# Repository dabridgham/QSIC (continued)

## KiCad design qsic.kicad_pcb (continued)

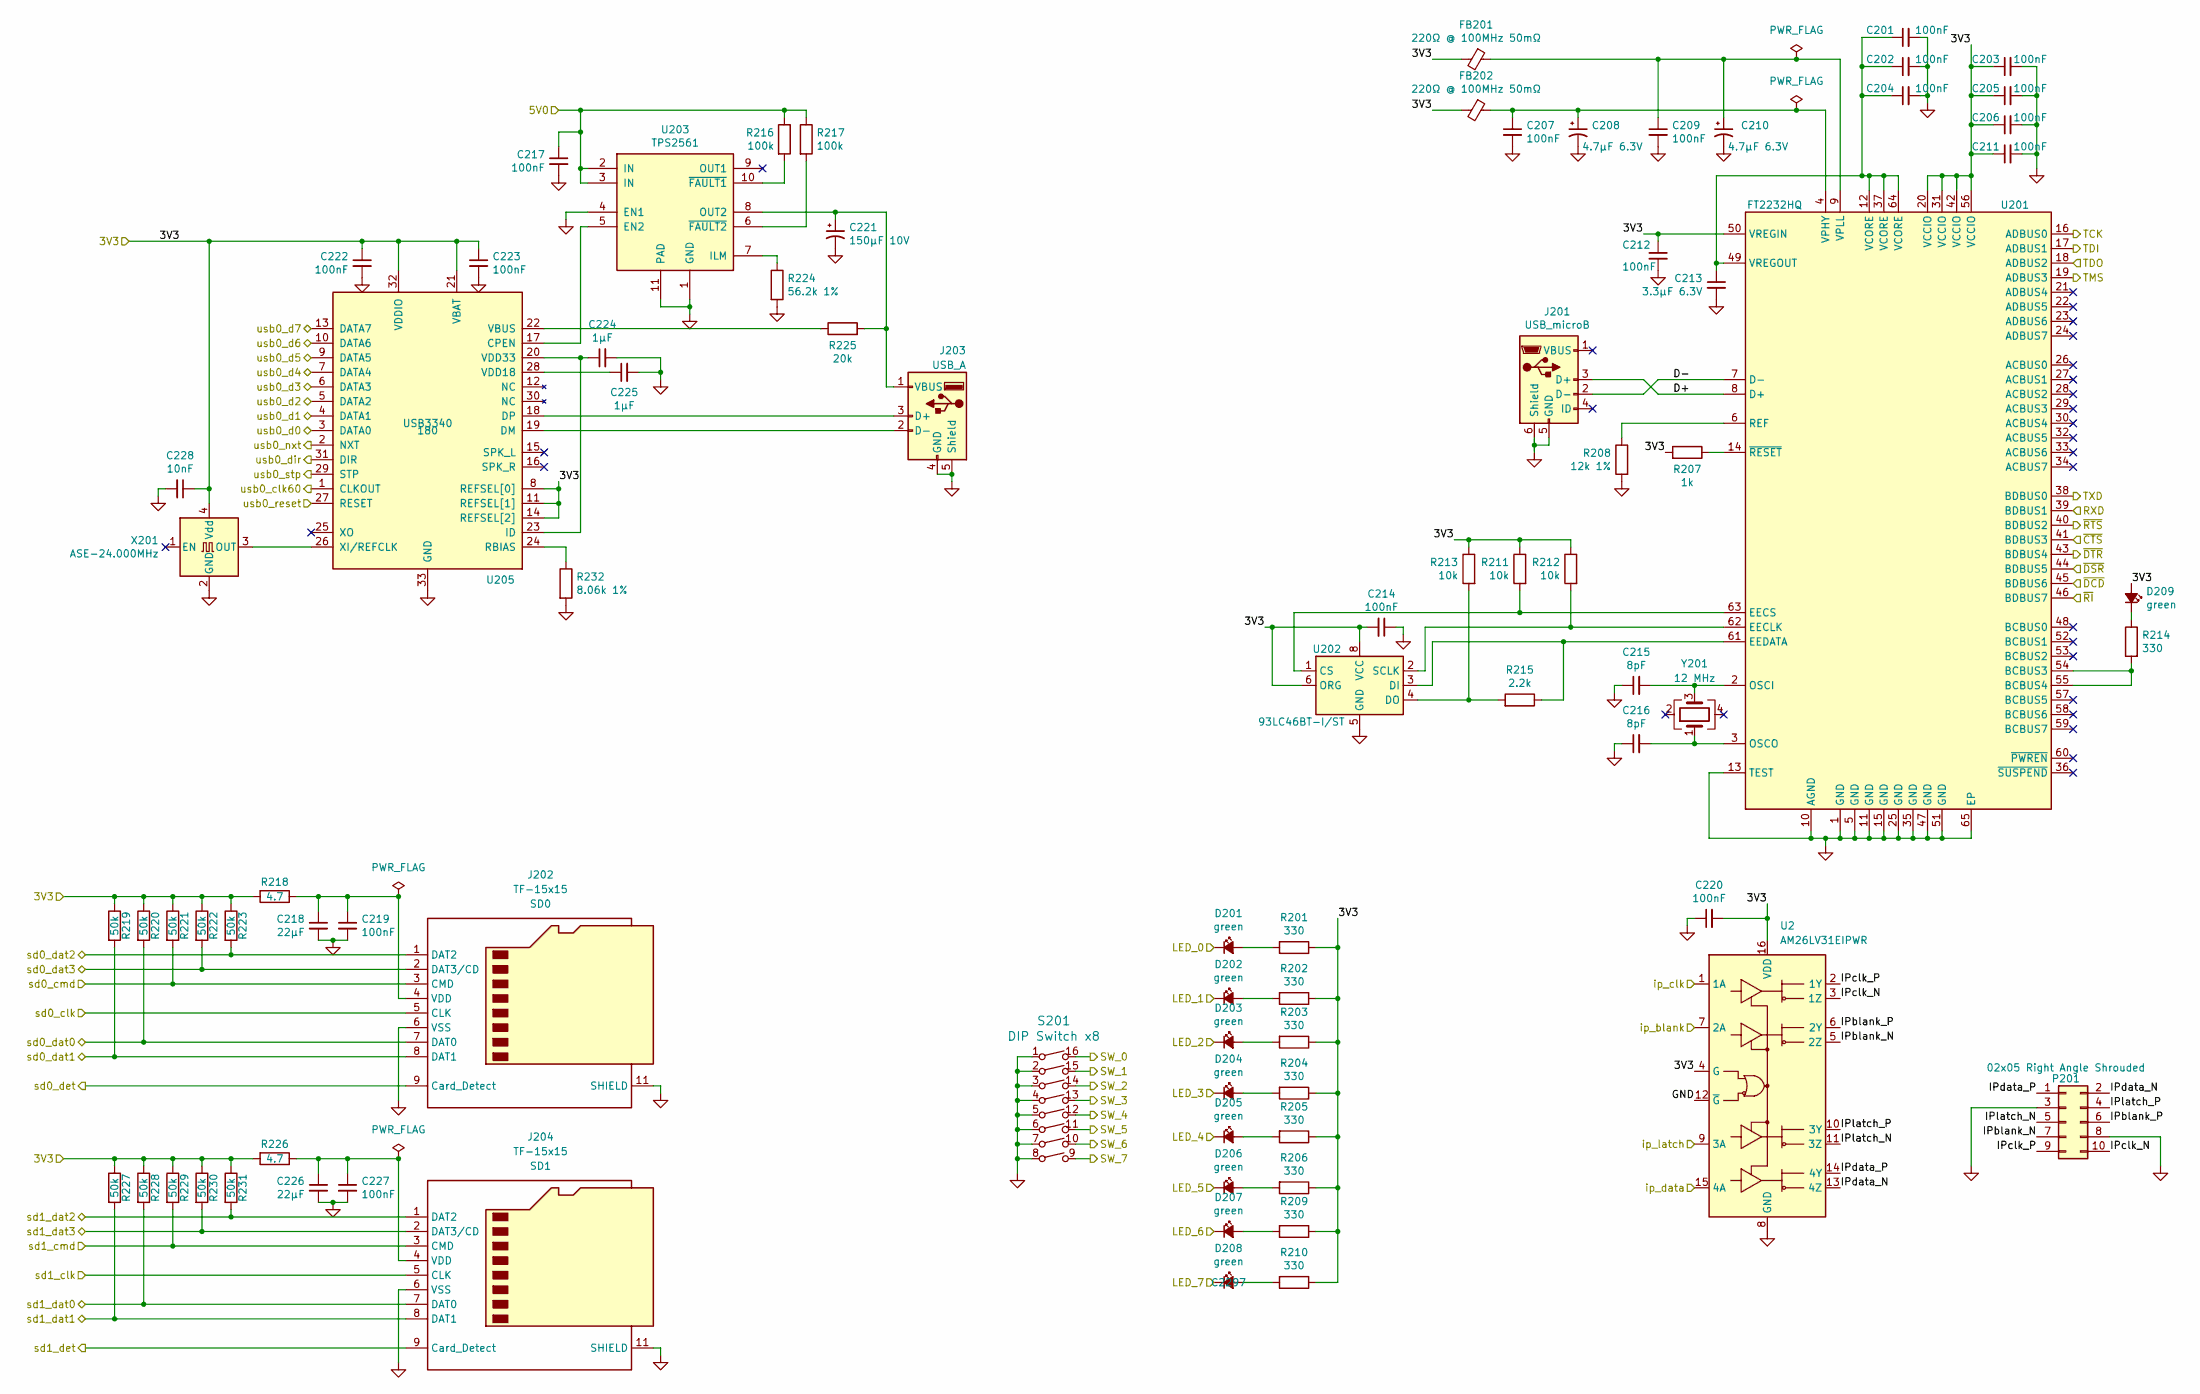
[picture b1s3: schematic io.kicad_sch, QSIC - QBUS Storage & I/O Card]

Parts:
C201, C202, C203, C204, C205, C206, C207, C209, C211, C212, C214, C217, C219, C220, C222, C223, C227: 100nF; C_0603_1608Metric; MPN CL10B104KO8NNNC
C208, C210: 4.7µF 6.3V; C_0603_1608Metric; MPN CL10A475KP8NNNC; JLCPCB Part C19666
C213: 3.3µF 6.3V; C_0603_1608Metric; MPN CL10A335KP8NNNC; JLCPCB Part C51412
C215, C216: 8pF; C_0603_1608Metric; MPN CL10C8R2DB8NNNC
C218, C226: 22µF; C_0603_1608Metric; MPN CL10A226MP8NUNE; JLCPCB Part C59461
C221: 150µF 10V; C_Elec_6.3x7.7; MPN EEEFTV151XAP; JLCPCB Part C178603
C224, C225: 1µF; C_0603_1608Metric; MPN CL10B105KO8NNNC; JLCPCB Part C15849
C228: 10nF; C_0603_1608Metric; MPN CL10B103KB8NNNC
D201, D202, D203, D204, D205, D206, D207, D208, D209: green; LED_0603_1608Metric; MPN LTST-C190KGKT; JLCPCB Part C2297
FB201, FB202: 220Ω @ 100MHz 50mΩ; L_0805_2012Metric; MPN 742792022; JLCPCB Part C2661452
J201: USB_microB; USB_Micro-B_Molex_47346-0001; MPN 47346-0001; JLCPCB Part C132560
J202, J204: TF-15x15; TF15X15
J203: USB_A; Amphenol_87583_USB_A; MPN 87583-3010; JLCPCB Part C599120
P201: 02x05 Right Angle Shrouded; Box_Header_2x05_P2.54mm; MPN SBH11-PBPC-D05-RA-BK; JLCPCB Part C7434504
R201, R202, R203, R204, R205, R206, R209, R210, R214: 330; R_0603_1608Metric; MPN RC0603FR-07330RL
R207: 1k; R_0603_1608Metric; MPN RC0603FR-071KL
R208: 12k 1%; R_0603_1608Metric; MPN RC0603FR-0712KL
R211, R212, R213: 10k; R_0603_1608Metric; MPN RC0603FR-0710KL
R215: 2.2k; R_0603_1608Metric; MPN RC0603FR-072K2L
R216, R217: 100k; R_0603_1608Metric; MPN RC0603FR-07100KL
R218, R226: 4.7; R_0603_1608Metric; MPN RC0603FR-074R7L
R219, R220, R221, R222, R223, R227, R228, R229, R230, R231: 50k; R_0603_1608Metric; MPN RC0603FR-0749K9L
R224: 56.2k 1%; R_0603_1608Metric; MPN RC0603FR-0756K2L; JLCPCB Part C482887
R225: 20k; R_0603_1608Metric; MPN RC0603FR-0720KL
R232: 8.06k 1%; R_0603_1608Metric; MPN RC0603FR-078K06L; JLCPCB Part C131052
S201: DIP Switch x8; SW_DIP_SPSTx08_Slide_Omron_A6S-810x_W8.9mm_P2.54mm; MPN A6S-8101-H; JLCPCB Part C319032
U2: AM26LV31EIPWR; TSSOP-16_4.4x5mm_P0.65mm; MPN AM26LV31EIPWR; JLCPCB Part C527447
U201: FT2232HQ; QFN-64-1EP_9x9mm_P0.5mm_EP4.35x4.35mm_ThermalVias; MPN FT2232HQ
U202: 93LC46BT-I/ST; TSSOP-8_4.4x3mm_P0.65mm; MPN 93LC46BC-IST
U203: TPS2561; VSON-10-1EP_3x3mm_P0.5mm_EP1.65x2.4mm_ThermalVias; MPN TPS2561DRCR
U205: USB3340; QFN-32-1EP_5x5mm_P0.5mm_EP3.3x3.3mm; MPN USB3340-EZK
X201: ASE-24.000MHz; Oscillator_SMD_Abracon_ASE-4Pin_3.2x2.5mm; MPN ASE-24.000MHZ-LC-T
Y201: 12 MHz; Crystal_SMD_Abracon_ABM10-4Pin_2.5x2.0mm; MPN ABM10-167-12.000MHZ-T3

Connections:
/3V3: C203.1, C205.1, C206.1, C211.1, C212.1, C214.2, C220.2, C222.1, C223.1, C228.1, D209.2 (A), FB201.2, FB202.2, R201.1, R202.1, R203.1, R204.1, R205.1, R206.1, R207.2, R209.1, R210.1, R211.1, R212.1, R213.1, R218.2, R219.1, R220.1, R221.1, R222.1, R223.1, R226.2, R227.1, R228.1, R229.1, R230.1, R231.1, U2.4 (G), U2.16 (VDD), U201.20 (VCCIO), U201.31 (VCCIO), U201.42 (VCCIO), U201.50 (VREGIN), U201.56 (VCCIO), U202.6 (ORG), U202.8 (VCC), U205.8 (REFSEL[0]), U205.11 (REFSEL[1]), U205.14 (REFSEL[2]), U205.21 (VBAT), U205.32 (VDDIO), X201.4 (Vdd); also elsewhere on the board
/5V0: C217.1, R216.1, R217.1, U203.2 (IN), U203.3 (IN); also elsewhere on the board
/IO/D+: J201.3 (D+), U201.8 (D+)
/IO/D-: J201.2 (D-), U201.7 (D-)
/IO/IPblank_N: P201.7, U2.5 (2Z)
/IO/IPblank_P: P201.6, U2.6 (2Y)
/IO/IPclk_N: P201.10, U2.3 (1Z)
/IO/IPclk_P: P201.9, U2.2 (1Y)
/IO/IPdata_N: P201.2, U2.13 (4Z)
/IO/IPdata_P: P201.1, U2.14 (4Y)
/IO/IPlatch_N: P201.5, U2.11 (3Z)
/IO/IPlatch_P: P201.4, U2.10 (3Y)
/LED_0: D201.1 (K); also elsewhere on the board
/LED_1: D202.1 (K); also elsewhere on the board
/LED_2: D203.1 (K); also elsewhere on the board
/LED_3: D204.1 (K); also elsewhere on the board
/LED_4: D205.1 (K); also elsewhere on the board
/LED_5: D206.1 (K); also elsewhere on the board
/LED_6: D207.1 (K); also elsewhere on the board
/LED_7: D208.1 (K); also elsewhere on the board
/RXD: U201.39 (BDBUS1); also elsewhere on the board
/SW_0: S201.16; also elsewhere on the board
/SW_1: S201.15; also elsewhere on the board
/SW_2: S201.14; also elsewhere on the board
/SW_3: S201.13; also elsewhere on the board
/SW_4: S201.12; also elsewhere on the board
/SW_5: S201.11; also elsewhere on the board
/SW_6: S201.10; also elsewhere on the board
/SW_7: S201.9; also elsewhere on the board
/TCK: U201.16 (ADBUS0); also elsewhere on the board
/TDI: U201.17 (ADBUS1); also elsewhere on the board
/TDO: U201.18 (ADBUS2); also elsewhere on the board
/TMS: U201.19 (ADBUS3); also elsewhere on the board
/TXD: U201.38 (BDBUS0); also elsewhere on the board
/ip_blank: U2.7 (2A); also elsewhere on the board
/ip_clk: U2.1 (1A); also elsewhere on the board
/ip_data: U2.15 (4A); also elsewhere on the board
/ip_latch: U2.9 (3A); also elsewhere on the board
/sd0_clk: J202.5 (CLK); also elsewhere on the board
/sd0_cmd: J202.3 (CMD), R221.2; also elsewhere on the board
/sd0_dat0: J202.7 (DAT0), R220.2; also elsewhere on the board
/sd0_dat1: J202.8 (DAT1), R219.2; also elsewhere on the board
/sd0_dat2: J202.1 (DAT2), R223.2; also elsewhere on the board
/sd0_dat3: J202.2 (DAT3/CD), R222.2; also elsewhere on the board
/sd0_det: J202.9 (Card_Detect); also elsewhere on the board
/sd1_clk: J204.5 (CLK); also elsewhere on the board
/sd1_cmd: J204.3 (CMD), R229.2; also elsewhere on the board
/sd1_dat0: J204.7 (DAT0), R228.2; also elsewhere on the board
/sd1_dat1: J204.8 (DAT1), R227.2; also elsewhere on the board
/sd1_dat2: J204.1 (DAT2), R231.2; also elsewhere on the board
/sd1_dat3: J204.2 (DAT3/CD), R230.2; also elsewhere on the board
/sd1_det: J204.9 (Card_Detect); also elsewhere on the board
/usb0_clk60: U205.1 (CLKOUT); also elsewhere on the board
/usb0_d0: U205.3 (DATA0); also elsewhere on the board
/usb0_d1: U205.4 (DATA1); also elsewhere on the board
/usb0_d2: U205.5 (DATA2); also elsewhere on the board
/usb0_d3: U205.6 (DATA3); also elsewhere on the board
/usb0_d4: U205.7 (DATA4); also elsewhere on the board
/usb0_d5: U205.9 (DATA5); also elsewhere on the board
/usb0_d6: U205.10 (DATA6); also elsewhere on the board
/usb0_d7: U205.13 (DATA7); also elsewhere on the board
/usb0_dir: U205.31 (DIR); also elsewhere on the board
/usb0_nxt: U205.2 (NXT); also elsewhere on the board
/usb0_reset: U205.27 (RESET); also elsewhere on the board
/usp0_stp: U205.29 (STP); also elsewhere on the board
/~CTS: U201.41 (BDBUS3); also elsewhere on the board
/~DCD: U201.45 (BDBUS6); also elsewhere on the board
/~DSR: U201.44 (BDBUS5); also elsewhere on the board
/~DTR: U201.43 (BDBUS4); also elsewhere on the board
/~RI: U201.46 (BDBUS7); also elsewhere on the board
/~RTS: U201.40 (BDBUS2); also elsewhere on the board
GND: C201.2, C202.2, C203.2, C204.2, C205.2, C206.2, C207.2, C208.2, C209.2, C210.2, C211.2, C212.2, C213.2, C214.1, C215.1, C216.1, C217.2, C218.2, C219.2, C220.1, C221.2, C222.2, C223.2, C224.2, C225.2, C226.2, C227.2, C228.2, J201.5 (GND), J201.6 (Shield), J202.6 (VSS), J202.11 (SHIELD), J203.4 (GND), J203.5 (Shield), J204.6 (VSS), J204.11 (SHIELD), P201.3, P201.8, R208.2, R224.2, R232.2, S201.1, S201.2, S201.3, S201.4, S201.5, S201.6, S201.7, S201.8, U2.8 (GND), U2.12 (~G), U201.1 (GND), U201.5 (GND), U201.10 (AGND), U201.11 (GND), U201.13 (TEST), U201.15 (GND), U201.25 (GND), U201.35 (GND), U201.47 (GND), U201.51 (GND), U201.65 (EP), U202.5 (GND), U203.1 (GND), U203.4 (EN1), U203.11 (PAD), U205.33 (GND), X201.2 (GND); also elsewhere on the board
unnamed: D201.2 (A), R201.2
unnamed: D202.2 (A), R202.2
unnamed: D203.2 (A), R203.2
unnamed: D204.2 (A), R204.2
unnamed: D205.2 (A), R205.2
unnamed: D206.2 (A), R206.2
unnamed: D207.2 (A), R209.2
unnamed: D208.2 (A), R210.2
unnamed: D209.1 (K), R214.1
unnamed: C218.1, C219.1, J202.4 (VDD), R218.1
unnamed: J203.3 (D+), U205.18 (DP)
unnamed: J203.2 (D-), U205.19 (DM)
unnamed: C221.1, J203.1 (VBUS), R225.2, U203.8 (OUT2)
unnamed: C226.1, C227.1, J204.4 (VDD), R226.1
unnamed: R214.2, U201.54 (BCBUS3), U201.55 (BCBUS4)
unnamed: R212.2, U201.62 (EECLK), U202.2 (SCLK)
unnamed: R211.2, U201.63 (EECS), U202.1 (CS)
unnamed: R215.1, U201.61 (EEDATA), U202.3 (DI)
unnamed: C215.2, U201.2 (OSCI), Y201.3
unnamed: C216.2, U201.3 (OSCO), Y201.1
unnamed: R208.1, U201.6 (REF)
unnamed: C207.1, C208.1, FB202.1, U201.4 (VPHY)
unnamed: C209.1, C210.1, FB201.1, U201.9 (VPLL)
unnamed: C201.1, C202.1, C204.1, C213.1, U201.12 (VCORE), U201.37 (VCORE), U201.49 (VREGOUT), U201.64 (VCORE)
unnamed: R207.1, U201.14 (~RESET)
unnamed: R213.2, R215.2, U202.4 (DO)
unnamed: U203.5 (EN2), U205.17 (CPEN)
unnamed: R224.1, U203.7 (ILM)
unnamed: R216.2, U203.10 (~FAULT1)
unnamed: R217.2, U203.6 (~FAULT2)
unnamed: C224.1, U205.20 (VDD33), U205.23 (ID)
unnamed: R232.1, U205.24 (RBIAS)
unnamed: R225.1, U205.22 (VBUS)
unnamed: C225.1, U205.28 (VDD18)
unnamed: U205.26 (XI/REFCLK), X201.3 (OUT)

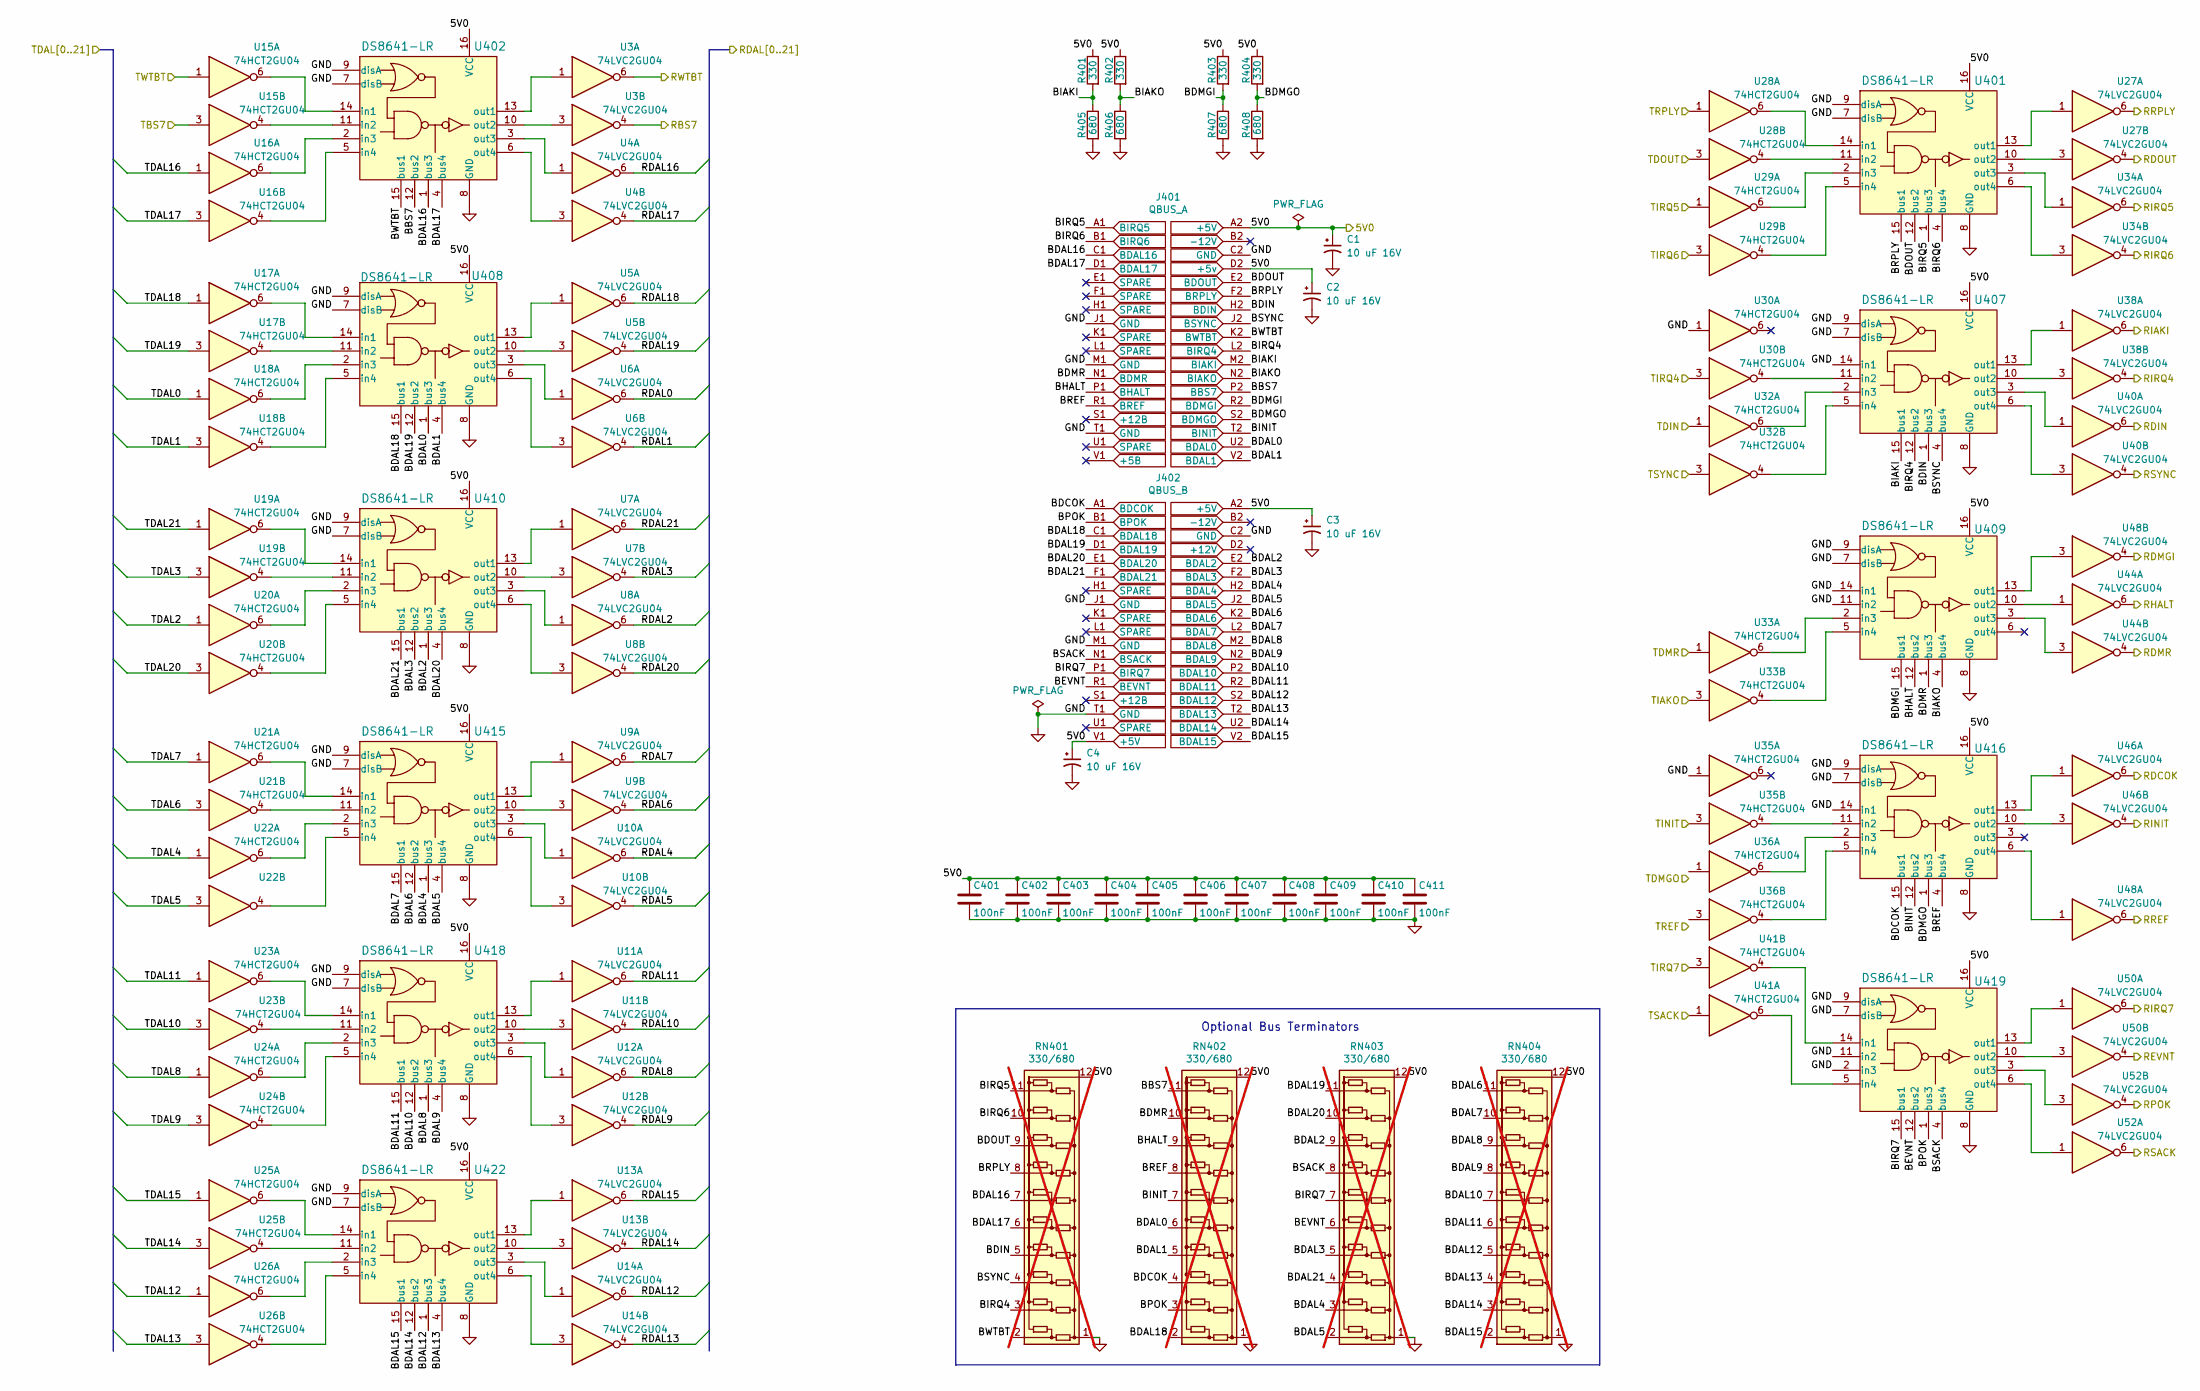
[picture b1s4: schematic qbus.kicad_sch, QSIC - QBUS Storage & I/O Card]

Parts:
C1, C2, C3, C4: 10 uF 16V; CP_EIA-3216-18_Kemet-A
C401, C402, C403, C404, C405, C406, C407, C408, C409, C410, C411: 100nF; C_0603_1608Metric; MPN CL10B104KO8NNNC
J401: QBUS_A; DEC_Edge_Fingers_single_height-1
J402: QBUS_B; DEC_Edge_Fingers_single_height-1
R401, R402, R403, R404: 330; R_0603_1608Metric; MPN RC0603FR-07330RL
R405, R406, R407, R408: 680; R_0603_1608Metric; MPN RC0603FR-07680RL
RN401, RN402, RN403, RN404: 330/680; R_Array_SIP12; MPN 4612X-104-331/681L; not fitted
U3, U4, U5, U6, U7, U8, U9, U10, U11, U12, U13, U14, U27, U34, U38, U40, U44, U46, U48, U50, U52: 74LVC2GU04; SOT-363_SC-70-6
U15, U16, U17, U18, U19, U20, U21, U22, U23, U24, U25, U26, U28, U29, U30, U32, U33, U35, U36, U41: 74HCT2GU04; SOT-363_SC-70-6
U401, U402, U407, U408, U409, U410, U415, U416, U418, U419, U422: DS8641-LR; DIP-16_W7.62mm; MPN DS8641

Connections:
/5V0: C1.1, C2.1, C3.1, C4.1, C401.1, C402.1, C403.1, C404.1, C405.1, C406.1, C407.1, C408.1, C409.1, C410.1, C411.1, J401.A2 (+5V), J401.D2 (+5v), J402.A2 (+5V), J402.V1 (+5V), R401.1, R402.1, R403.1, R404.1, RN401.12 (COM2), RN402.12 (COM2), RN403.12 (COM2), RN404.12 (COM2), U401.16 (VCC), U402.16 (VCC), U407.16 (VCC), U408.16 (VCC), U409.16 (VCC), U410.16 (VCC), U415.16 (VCC), U416.16 (VCC), U418.16 (VCC), U419.16 (VCC), U422.16 (VCC); also elsewhere on the board
/QBUS/BBS7: J401.P2 (BBS7), RN402.11 (R10), U402.12 (bus2)
/QBUS/BDAL0: J401.U2 (BDAL0), RN402.6 (R5), U408.1 (bus3)
/QBUS/BDAL1: J401.V2 (BDAL1), RN402.5 (R4), U408.4 (bus4)
/QBUS/BDAL2: J402.E2 (BDAL2), RN403.9 (R8), U410.1 (bus3)
/QBUS/BDAL3: J402.F2 (BDAL3), RN403.5 (R4), U410.12 (bus2)
/QBUS/BDAL4: J402.H2 (BDAL4), RN403.3 (R2), U415.1 (bus3)
/QBUS/BDAL5: J402.J2 (BDAL5), RN403.2 (R1), U415.4 (bus4)
/QBUS/BDAL6: J402.K2 (BDAL6), RN404.11 (R10), U415.12 (bus2)
/QBUS/BDAL7: J402.L2 (BDAL7), RN404.10 (R9), U415.15 (bus1)
/QBUS/BDAL8: J402.M2 (BDAL8), RN404.9 (R8), U418.1 (bus3)
/QBUS/BDAL9: J402.N2 (BDAL9), RN404.8 (R7), U418.4 (bus4)
/QBUS/BDAL10: J402.P2 (BDAL10), RN404.7 (R6), U418.12 (bus2)
/QBUS/BDAL11: J402.R2 (BDAL11), RN404.6 (R5), U418.15 (bus1)
/QBUS/BDAL12: J402.S2 (BDAL12), RN404.5 (R4), U422.1 (bus3)
/QBUS/BDAL13: J402.T2 (BDAL13), RN404.4 (R3), U422.4 (bus4)
/QBUS/BDAL14: J402.U2 (BDAL14), RN404.3 (R2), U422.12 (bus2)
/QBUS/BDAL15: J402.V2 (BDAL15), RN404.2 (R1), U422.15 (bus1)
/QBUS/BDAL16: J401.C1 (BDAL16), RN401.7 (R6), U402.1 (bus3)
/QBUS/BDAL17: J401.D1 (BDAL17), RN401.6 (R5), U402.4 (bus4)
/QBUS/BDAL18: J402.C1 (BDAL18), RN402.2 (R1), U408.15 (bus1)
/QBUS/BDAL19: J402.D1 (BDAL19), RN403.11 (R10), U408.12 (bus2)
/QBUS/BDAL20: J402.E1 (BDAL20), RN403.10 (R9), U410.4 (bus4)
/QBUS/BDAL21: J402.F1 (BDAL21), RN403.4 (R3), U410.15 (bus1)
/QBUS/BDCOK: J402.A1 (BDCOK), RN402.4 (R3), U416.15 (bus1)
/QBUS/BDIN: J401.H2 (BDIN), RN401.5 (R4), U407.1 (bus3)
/QBUS/BDMGI: J401.R2 (BDMGI), R403.2, R407.1, U409.15 (bus1)
/QBUS/BDMGO: J401.S2 (BDMGO), R404.2, R408.1, U416.1 (bus3)
/QBUS/BDMR: J401.N1 (BDMR), RN402.10 (R9), U409.1 (bus3)
/QBUS/BDOUT: J401.E2 (BDOUT), RN401.9 (R8), U401.12 (bus2)
/QBUS/BEVNT: J402.R1 (BEVNT), RN403.6 (R5), U419.12 (bus2)
/QBUS/BHALT: J401.P1 (BHALT), RN402.9 (R8), U409.12 (bus2)
/QBUS/BIAKI: J401.M2 (BIAKI), R401.2, R405.1, U407.15 (bus1)
/QBUS/BIAKO: J401.N2 (BIAKO), R402.2, R406.1, U409.4 (bus4)
/QBUS/BINIT: J401.T2 (BINIT), RN402.7 (R6), U416.12 (bus2)
/QBUS/BIRQ4: J401.L2 (BIRQ4), RN401.3 (R2), U407.12 (bus2)
/QBUS/BIRQ5: J401.A1 (BIRQ5), RN401.11 (R10), U401.1 (bus3)
/QBUS/BIRQ6: J401.B1 (BIRQ6), RN401.10 (R9), U401.4 (bus4)
/QBUS/BIRQ7: J402.P1 (BIRQ7), RN403.7 (R6), U419.15 (bus1)
/QBUS/BPOK: J402.B1 (BPOK), RN402.3 (R2), U419.1 (bus3)
/QBUS/BREF: J401.R1 (BREF), RN402.8 (R7), U416.4 (bus4)
/QBUS/BRPLY: J401.F2 (BRPLY), RN401.8 (R7), U401.15 (bus1)
/QBUS/BSACK: J402.N1 (BSACK), RN403.8 (R7), U419.4 (bus4)
/QBUS/BSYNC: J401.J2 (BSYNC), RN401.4 (R3), U407.4 (bus4)
/QBUS/BWTBT: J401.K2 (BWTBT), RN401.2 (R1), U402.15 (bus1)
/RBS7: U3.4; also elsewhere on the board
/RDAL0: U6.6; also elsewhere on the board
/RDAL1: U6.4; also elsewhere on the board
/RDAL2: U8.6; also elsewhere on the board
/RDAL3: U7.4; also elsewhere on the board
/RDAL4: U10.6; also elsewhere on the board
/RDAL5: U10.4; also elsewhere on the board
/RDAL6: U9.4; also elsewhere on the board
/RDAL7: U9.6; also elsewhere on the board
/RDAL8: U12.6; also elsewhere on the board
/RDAL9: U12.4; also elsewhere on the board
/RDAL10: U11.4; also elsewhere on the board
/RDAL11: U11.6; also elsewhere on the board
/RDAL12: U14.6; also elsewhere on the board
/RDAL13: U14.4; also elsewhere on the board
/RDAL14: U13.4; also elsewhere on the board
/RDAL15: U13.6; also elsewhere on the board
/RDAL16: U4.6; also elsewhere on the board
/RDAL17: U4.4; also elsewhere on the board
/RDAL18: U5.6; also elsewhere on the board
/RDAL19: U5.4; also elsewhere on the board
/RDAL20: U8.4; also elsewhere on the board
/RDAL21: U7.6; also elsewhere on the board
/RDCOK: U46.6; also elsewhere on the board
/RDIN: U40.6; also elsewhere on the board
/RDMGI: U48.4; also elsewhere on the board
/RDMR: U44.4; also elsewhere on the board
/RDOUT: U27.4; also elsewhere on the board
/REVNT: U50.4; also elsewhere on the board
/RHALT: U44.6; also elsewhere on the board
/RIAKI: U38.6; also elsewhere on the board
/RINIT: U46.4; also elsewhere on the board
/RIRQ4: U38.4; also elsewhere on the board
/RIRQ5: U34.6; also elsewhere on the board
/RIRQ6: U34.4; also elsewhere on the board
/RIRQ7: U50.6; also elsewhere on the board
/RPOK: U52.4; also elsewhere on the board
/RREF: U48.6; also elsewhere on the board
/RRPLY: U27.6; also elsewhere on the board
/RSACK: U52.6; also elsewhere on the board
/RSYNC: U40.4; also elsewhere on the board
/RWTBT: U3.6; also elsewhere on the board
/TBS7: U15.3; also elsewhere on the board
/TDAL0: U18.1; also elsewhere on the board
/TDAL1: U18.3; also elsewhere on the board
/TDAL2: U20.1; also elsewhere on the board
/TDAL3: U19.3; also elsewhere on the board
/TDAL4: U22.1; also elsewhere on the board
/TDAL5: U22.3; also elsewhere on the board
/TDAL6: U21.3; also elsewhere on the board
/TDAL7: U21.1; also elsewhere on the board
/TDAL8: U24.1; also elsewhere on the board
/TDAL9: U24.3; also elsewhere on the board
/TDAL10: U23.3; also elsewhere on the board
/TDAL11: U23.1; also elsewhere on the board
/TDAL12: U26.1; also elsewhere on the board
/TDAL13: U26.3; also elsewhere on the board
/TDAL14: U25.3; also elsewhere on the board
/TDAL15: U25.1; also elsewhere on the board
/TDAL16: U16.1; also elsewhere on the board
/TDAL17: U16.3; also elsewhere on the board
/TDAL18: U17.1; also elsewhere on the board
/TDAL19: U17.3; also elsewhere on the board
/TDAL20: U20.3; also elsewhere on the board
/TDAL21: U19.1; also elsewhere on the board
/TDIN: U32.1; also elsewhere on the board
/TDMR: U33.1; also elsewhere on the board
/TDOUT: U28.3; also elsewhere on the board
/TIAKO: U33.3; also elsewhere on the board
/TINIT: U35.3; also elsewhere on the board
/TIRQ4: U30.3; also elsewhere on the board
/TIRQ5: U29.1; also elsewhere on the board
/TIRQ6: U29.3; also elsewhere on the board
/TIRQ7: U41.3; also elsewhere on the board
/TRPLY: U28.1; also elsewhere on the board
/TSACK: U41.1; also elsewhere on the board
/TSYNC: U32.3; also elsewhere on the board
/TWTBT: U15.1; also elsewhere on the board
GND: C1.2, C2.2, C3.2, C4.2, C401.2, C402.2, C403.2, C404.2, C405.2, C406.2, C407.2, C408.2, C409.2, C410.2, C411.2, J401.C2 (GND), J401.J1 (GND), J401.M1 (GND), J401.T1 (GND), J402.C2 (GND), J402.J1 (GND), J402.M1 (GND), J402.T1 (GND), R405.2, R406.2, R407.2, R408.2, RN401.1 (COM1), RN402.1 (COM1), RN403.1 (COM1), RN404.1 (COM1), U30.1, U35.1, U401.7 (disB), U401.8 (GND), U401.9 (disA), U402.7 (disB), U402.8 (GND), U402.9 (disA), U407.7 (disB), U407.8 (GND), U407.9 (disA), U407.14 (in1), U408.7 (disB), U408.8 (GND), U408.9 (disA), U409.7 (disB), U409.8 (GND), U409.9 (disA), U409.11 (in2), U409.14 (in1), U410.7 (disB), U410.8 (GND), U410.9 (disA), U415.7 (disB), U415.8 (GND), U415.9 (disA), U416.7 (disB), U416.8 (GND), U416.9 (disA), U416.14 (in1), U418.7 (disB), U418.8 (GND), U418.9 (disA), U419.2 (in3), U419.7 (disB), U419.8 (GND), U419.9 (disA), U419.11 (in2), U422.7 (disB), U422.8 (GND), U422.9 (disA); also elsewhere on the board
unnamed: U28.6, U401.14 (in1)
unnamed: U28.4, U401.11 (in2)
unnamed: U29.6, U401.2 (in3)
unnamed: U29.4, U401.5 (in4)
unnamed: U27.1, U401.13 (out1)
unnamed: U27.3, U401.10 (out2)
unnamed: U34.1, U401.3 (out3)
unnamed: U34.3, U401.6 (out4)
unnamed: U15.6, U402.14 (in1)
unnamed: U15.4, U402.11 (in2)
unnamed: U16.6, U402.2 (in3)
unnamed: U16.4, U402.5 (in4)
unnamed: U3.1, U402.13 (out1)
unnamed: U3.3, U402.10 (out2)
unnamed: U4.1, U402.3 (out3)
unnamed: U4.3, U402.6 (out4)
unnamed: U30.4, U407.11 (in2)
unnamed: U32.6, U407.2 (in3)
unnamed: U32.4, U407.5 (in4)
unnamed: U38.1, U407.13 (out1)
unnamed: U38.3, U407.10 (out2)
unnamed: U40.1, U407.3 (out3)
unnamed: U40.3, U407.6 (out4)
unnamed: U17.6, U408.14 (in1)
unnamed: U17.4, U408.11 (in2)
unnamed: U18.6, U408.2 (in3)
unnamed: U18.4, U408.5 (in4)
unnamed: U5.1, U408.13 (out1)
unnamed: U5.3, U408.10 (out2)
unnamed: U6.1, U408.3 (out3)
unnamed: U6.3, U408.6 (out4)
unnamed: U33.6, U409.2 (in3)
unnamed: U33.4, U409.5 (in4)
unnamed: U48.3, U409.13 (out1)
unnamed: U44.1, U409.10 (out2)
unnamed: U44.3, U409.3 (out3)
unnamed: U19.6, U410.14 (in1)
unnamed: U19.4, U410.11 (in2)
unnamed: U20.6, U410.2 (in3)
unnamed: U20.4, U410.5 (in4)
unnamed: U7.1, U410.13 (out1)
unnamed: U7.3, U410.10 (out2)
unnamed: U8.1, U410.3 (out3)
unnamed: U8.3, U410.6 (out4)
unnamed: U21.6, U415.14 (in1)
unnamed: U21.4, U415.11 (in2)
unnamed: U22.6, U415.2 (in3)
unnamed: U22.4, U415.5 (in4)
unnamed: U9.1, U415.13 (out1)
unnamed: U9.3, U415.10 (out2)
unnamed: U10.1, U415.3 (out3)
unnamed: U10.3, U415.6 (out4)
unnamed: U35.4, U416.11 (in2)
unnamed: U36.6, U416.2 (in3)
unnamed: U36.4, U416.5 (in4)
unnamed: U46.1, U416.13 (out1)
unnamed: U46.3, U416.10 (out2)
unnamed: U48.1, U416.6 (out4)
unnamed: U23.6, U418.14 (in1)
unnamed: U23.4, U418.11 (in2)
unnamed: U24.6, U418.2 (in3)
unnamed: U24.4, U418.5 (in4)
unnamed: U11.1, U418.13 (out1)
unnamed: U11.3, U418.10 (out2)
unnamed: U12.1, U418.3 (out3)
unnamed: U12.3, U418.6 (out4)
unnamed: U41.4, U419.14 (in1)
unnamed: U41.6, U419.5 (in4)
unnamed: U50.1, U419.13 (out1)
unnamed: U50.3, U419.10 (out2)
unnamed: U52.3, U419.3 (out3)
unnamed: U52.1, U419.6 (out4)
unnamed: U25.6, U422.14 (in1)
unnamed: U25.4, U422.11 (in2)
unnamed: U26.6, U422.2 (in3)
unnamed: U26.4, U422.5 (in4)
unnamed: U13.1, U422.13 (out1)
unnamed: U13.3, U422.10 (out2)
unnamed: U14.1, U422.3 (out3)
unnamed: U14.3, U422.6 (out4)

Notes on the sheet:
Optional Bus Terminators
